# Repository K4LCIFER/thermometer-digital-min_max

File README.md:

# Digital Min/Max Thermometer

# Introduction

The following project holds all the required files, and information to build a
battery powered digital min/max thermometer.

## Scope

The project is intended to be simple, reliable, and cheap.

## Directory Guide

- [Electronics (PCB, etc.)](./electronics)
- [Hardware (Case, etc.)](./hardware)
- [Firmware](./firmware)

## Donations

Monero (XMR): `8BG1wFgq4fTKhekEh58Ae1M1ShGUsp15yFXJUuCXYQiFKUmDuQ9BK8tTfUfvXV2WR1CPE5Ry6DY45DmdDQm3SiCY7Jkw5ws`
<details><summary>Click to show XMR QR-Code</summary>

</details>

Bitcoin (BTC): `bc1qvx8jt2qxar7thnxczqalzeyspd0xz8xr046edu`
<details><summary>Click to show BTC QR-Code</summary>

</details>

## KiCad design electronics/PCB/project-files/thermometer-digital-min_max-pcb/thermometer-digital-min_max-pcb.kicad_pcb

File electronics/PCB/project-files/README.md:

This PCB is designed with [KiCAD](https://www.kicad.org/) v6.0.7

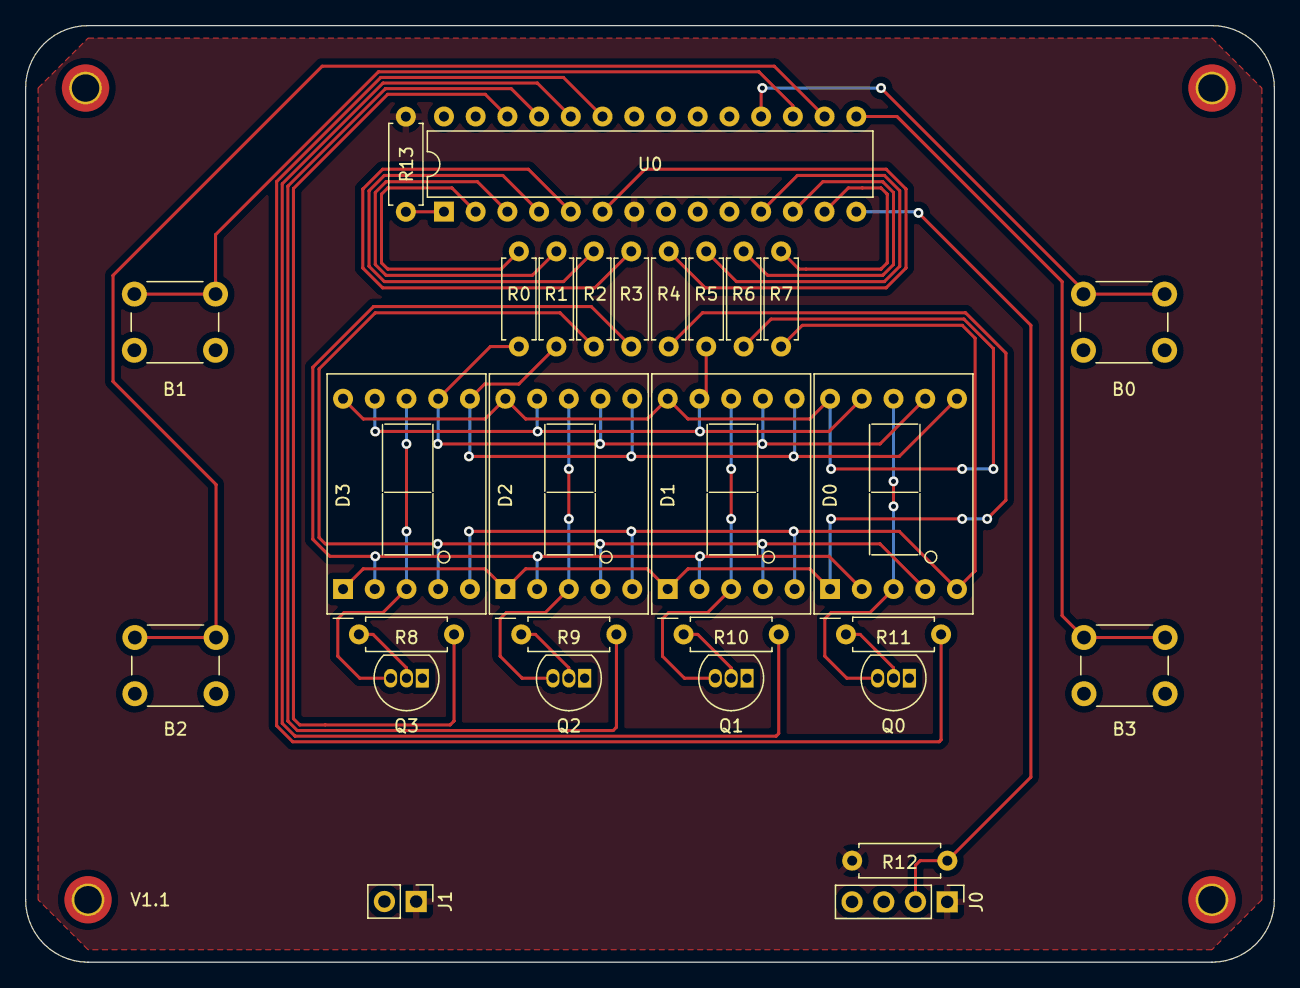
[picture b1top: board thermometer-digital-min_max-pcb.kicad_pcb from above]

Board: 2 copper layers, 100.0 x 75.0 mm, 29 parts (0 on the bottom side), 36 nets.

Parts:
B0: disp_current_temp; SW_PUSH_6mm_H9.5mm
B1: disp_max_temp; SW_PUSH_6mm_H9.5mm
B2: disp_min_temp; SW_PUSH_6mm_H9.5mm
B3: reset_saved_temps; SW_PUSH_6mm_H9.5mm
D0, D1, D2, D3: INND-TS56; D1X8K
J0: sensor_connection; PinHeader_1x04_P2.54mm_Vertical
J1: battery_connection; PinHeader_1x02_P2.54mm_Vertical
Q0, Q1, Q2, Q3: PN2222A; TO-92_Inline
R0, R1, R2, R3, R4, R5, R6, R7: 100R; R_Axial_DIN0207_L6.3mm_D2.5mm_P7.62mm_Horizontal
R8, R9, R10, R11: 680R; R_Axial_DIN0207_L6.3mm_D2.5mm_P7.62mm_Horizontal
R12: 4.7k; R_Axial_DIN0207_L6.3mm_D2.5mm_P7.62mm_Horizontal
R13: 10k; R_Axial_DIN0207_L6.3mm_D2.5mm_P7.62mm_Horizontal
U0: ATmega328P-U; DIP-28_W7.62mm

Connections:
/SS_A: D0.7 (A), D1.7 (A), D2.7 (A), D3.7 (A), R0.2
/SS_B: D0.6 (B), D1.6 (B), D2.6 (B), D3.6 (B), R1.2
/SS_C: D0.4 (C), D1.4 (C), D2.4 (C), D3.4 (C), R2.2
/SS_D: D0.2 (D), D1.2 (D), D2.2 (D), D3.2 (D), R3.2
/SS_DP: D0.5 (DP), D1.5 (DP), D2.5 (DP), D3.5 (DP), R7.2
/SS_E: D0.1 (E), D1.1 (E), D2.1 (E), D3.1 (E), R4.2
/SS_F: D0.9 (F), D1.9 (F), D2.9 (F), D3.9 (F), R5.2
/SS_G: D0.10 (G), D1.10 (G), D2.10 (G), D3.10 (G), R6.2
GND: B0.2, B1.2, B2.2, B3.2, J0.3, J0.4, J1.2, Q0.1 (E), Q1.1 (E), Q2.1 (E), Q3.1 (E), U0.8 (GND), U0.9 (XTAL1/PB6), U0.10 (XTAL2/PB7), U0.19 (PB5), U0.20 (AVCC), U0.21 (AREF), U0.22 (GND), U0.27 (PC4), U0.28 (PC5)
unnamed: B0.1, U0.18 (PB4)
unnamed: B1.1, U0.17 (PB3)
unnamed: B2.1, U0.16 (PB2)
unnamed: B3.1, U0.15 (PB1)
unnamed: D0.3 (CC), D0.8 (CC), Q0.3 (C)
unnamed: D1.3 (CC), D1.8 (CC), Q1.3 (C)
unnamed: D2.3 (CC), D2.8 (CC), Q2.3 (C)
unnamed: D3.3 (CC), D3.8 (CC), Q3.3 (C)
unnamed: J0.2, R12.2, U0.14 (PB0)
unnamed: Q0.2 (B), R11.2
unnamed: Q1.2 (B), R10.2
unnamed: Q2.2 (B), R9.2
unnamed: Q3.2 (B), R8.2
unnamed: R0.1, U0.2 (PD0)
unnamed: R1.1, U0.3 (PD1)
unnamed: R2.1, U0.4 (PD2)
unnamed: R3.1, U0.5 (PD3)
unnamed: R4.1, U0.6 (PD4)
unnamed: R5.1, U0.11 (PD5)
unnamed: R6.1, U0.12 (PD6)
unnamed: R7.1, U0.13 (PD7)
unnamed: R8.1, U0.26 (PC3)
unnamed: R9.1, U0.25 (PC2)
unnamed: R10.1, U0.24 (PC1)
unnamed: R11.1, U0.23 (PC0)
unnamed: R13.1, U0.1 (~RESET/PC6)
VCC: J0.1, J1.1, R12.1, R13.2, U0.7 (VCC)

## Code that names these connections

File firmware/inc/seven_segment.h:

////////////////////////////////////////////////////////////////////////////////
// To use this header file, make sure that you define the name/series of the 
// 7 segment display that you will be using in your program code where this 
// header file is included.
////////////////////////////////////////////////////////////////////////////////

#ifndef _SEVEN_SEGMENT_H_
#define _SEVEN_SEGMENT_H_

#ifdef INND_TS56
//      SEVEN_SEGMENT_<X>   0b<DP><G><F><E><D><C><B><A>
#define _SS_A   0b00000001
#define _SS_B   0b00000010
#define _SS_C   0b00000100
#define _SS_D   0b00001000
#define _SS_E   0b00010000
#define _SS_F   0b00100000
#define _SS_G   0b01000000
#define _SS_DP  0b10000000

#define SS_0    _SS_A | _SS_B | _SS_C | _SS_D | _SS_E | _SS_F
#define SS_1    _SS_B | _SS_C
#define SS_2    _SS_A | _SS_B | _SS_G | _SS_E | _SS_D
#define SS_3    _SS_A | _SS_B | _SS_G | _SS_C | _SS_D
#define SS_4    _SS_F | _SS_G | _SS_B | _SS_C
#define SS_5    _SS_A | _SS_F | _SS_G | _SS_C | _SS_D
#define SS_6    _SS_A | _SS_F | _SS_G | _SS_C | _SS_D | _SS_E
#define SS_7    _SS_A | _SS_B | _SS_C
#define SS_8    _SS_A | _SS_B | _SS_C | _SS_D | _SS_E | _SS_F \
    | _SS_G
#define SS_9    _SS_A | _SS_F | _SS_B | _SS_G | _SS_C
#define SS_DEC  _SS_DP
#define SS_NEG  _SS_G
#define SS_CLEAR    0
#endif

#endif

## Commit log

2022-08-17 fixed a syntax error.
2022-08-17 Removed some magic numbers to increase readability.
2022-08-17 Changed a variable name to be more readable.
2022-08-17 Starting reorginasation
2022-08-17 Rewrite completely functional. Now all that is left is final polish, and documentation.
2022-08-17 Refactored a variable to be more accurate to its purpose.
2022-08-17 This version is crap. Just commiting for historical reasons.
2022-08-17 Done refactoring
2022-08-17 Started the PCB
2022-08-17 v1.0 of PCB
2022-08-17 Still trying to fix the sensor data issues
2022-08-17 - Rewrote the receive function, and the related interrupt routine(s). - I switched away from timing the high of the bit, to just capturing the entire bit period. - Added a checksum routine for the re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
2022-08-17 updated gitignore
2022-08-17 Got the data communication working. Issues with interrupt flags, compiler optimizations not being enabled, and many other minor bugs.
2022-08-17 Fixed a bunch of warnings.
2022-08-17 just commiting everything to clean up git. some firmware stuff was accidentally written while in the pcb branch. I'm too lazy to clean up the commits, so I'm just going to start from square one by co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
2022-08-17 refactored the file tree by moving the PCB files into the new electronics folder in the root directory.
2022-08-19 Testing signing
2022-08-19 Completed the relayout of the PCB
2022-08-19 Updated gerber files to match the new layout.
2022-08-19 Adjusted the position of the silkscreen for some components
2022-08-20 Moved existing datasheets to their respective subfolders
2022-08-20 Renamed electronics documentation files
2022-08-20 Renamed firmware documentation files
2022-08-20 Modified titles of datasheets
2022-08-20 Added parts list for PCB
2022-08-20 Removed unused dasheets
2022-08-20 Moved KiCAD gitignore to its most relevant subfolder
2022-08-20 Added empty PCB readme
2022-08-20 Added minor starting content to main project readme
2022-08-20 Refactored the pcb resources to contain a manufacturing directory that pertains to the manufacturing/assembly of the pcb, as well as a placeholder PCB specifications file
2022-08-20 Update the project files directory for KiCAD, moving its gitignore, and adding a README with info on the project files.
2022-08-20 Updated PCB README
2022-08-20 Added the started file that tracks PCB manufacturing specifications.
2022-08-20 Refactoring and documentation (#16)
    Added many starting point documentation files, and added documentation for the pcb, and firmware. Refactored some of the source tree so that it makes a bit more logical sense.
2022-08-20 Added the link to the kicad website
2022-08-20 Added a link to the KiCAD website in the KiCAD project files README
2022-08-20 Updated gerbers
2022-08-20 Updated PCB to v1.1
2022-08-20 Fixed gerbers. There were leftover layers from previous 4 layer.
2022-08-26 Moved freecad gitignore to the FreeCAD project files directory, and added a line to ignore .FCStd1 files
2022-08-26 Removed .FCStd1 files
2022-08-27 Fixed gitignore; forgot to specify the * before .FCStd1
2022-08-27 Added PCB pictures to the PCB README
2022-08-27 Fixed heading size for Images in PCB README
2022-08-27 Testing image filepaths in readme
2022-08-27 Fixed src for pictures in pcb readme
2022-08-27 Fixed image src for pcb readme
2022-08-27 Added PCB pictures to the PCB README (#20)
    Also added a folder for README resources relative to PCB: ./resouces/./README/*
